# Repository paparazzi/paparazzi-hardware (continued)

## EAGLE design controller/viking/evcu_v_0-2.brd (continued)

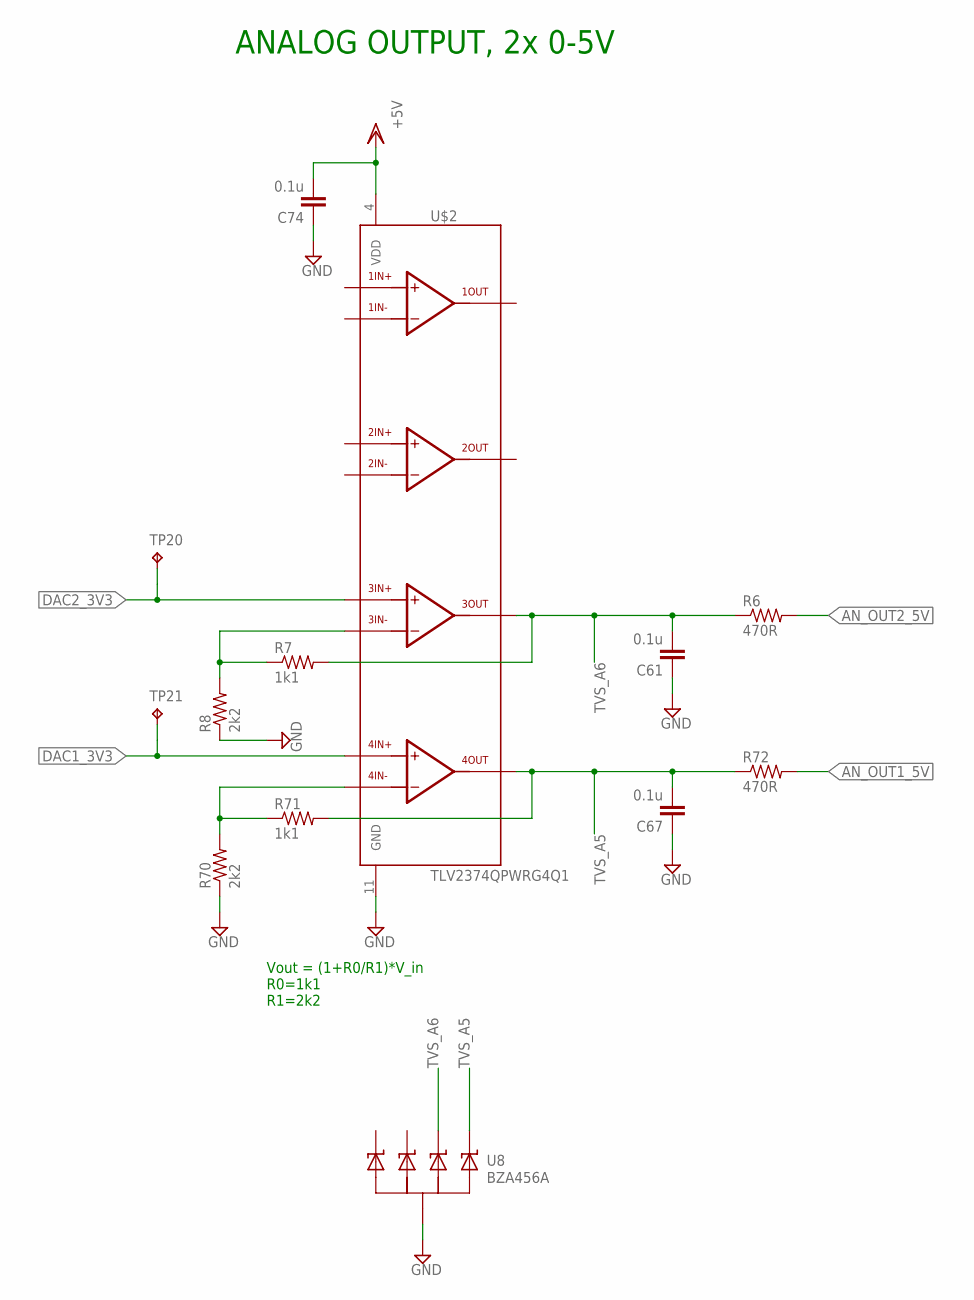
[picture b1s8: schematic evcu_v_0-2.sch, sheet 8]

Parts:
C61, C67, C74: 0.1u; C0603@1
R6, R72: 470R; R0603
R7, R71: 1k1; R0603
R8, R70: 2k2; R0603
TP20, TP21: TPB1,27; B1,27
U8: BZA456A; SOT457R_PHILIPS
U$2: TLV2374QPWRG4Q1; TSSOP14

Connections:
5V: C74.2, U$2.4 (VDD); also elsewhere on the board
AN_OUT1_5V: R72.2; also elsewhere on the board
AN_OUT2_5V: R6.2; also elsewhere on the board
DAC1_3V3: TP21.TP, U$2.12; also elsewhere on the board
DAC2_3V3: TP20.TP, U$2.10; also elsewhere on the board
GND: C61.1, C67.1, C74.1, R8.1, R70.1, U8.2 (COM), U8.5 (COM), U$2.11 (GND); also elsewhere on the board
unnamed: R7.1, R8.2, U$2.9
unnamed: R70.2, R71.1, U$2.13
TVS_A5: C67.2, R71.2, R72.1, U8.6 (C4), U$2.14
TVS_A6: C61.2, R6.1, R7.2, U8.4 (C3), U$2.8

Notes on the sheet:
ANALOG OUTPUT, 2x 0-5V
Vout = (1+R0/R1)*V_in R0=1k1 R1=2k2

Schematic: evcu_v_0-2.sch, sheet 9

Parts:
U$5: DEUTSCH_48_PIN

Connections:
5V: U$5.A$2, U$5.A$5, U$5.A$8, U$5.A$11; also elsewhere on the board
ANALOG_IN1_5V: U$5.A$3; also elsewhere on the board
ANALOG_IN2_5V: U$5.A$6; also elsewhere on the board
ANALOG_IN3_5V: U$5.A$9; also elsewhere on the board
ANALOG_IN4_5V: U$5.A$12; also elsewhere on the board
AN_OUT1_5V: U$5.C$2; also elsewhere on the board
AN_OUT2_5V: U$5.C$4; also elsewhere on the board
CAN1_H: U$5.C$7; also elsewhere on the board
CAN1_L: U$5.C$8; also elsewhere on the board
CAN2_H: U$5.C$11; also elsewhere on the board
CAN2_L: U$5.C$12; also elsewhere on the board
DIN_STB1: U$5.B$7; also elsewhere on the board
DIN_STB2: U$5.B$8; also elsewhere on the board
DIN_STB3: U$5.B$9; also elsewhere on the board
DIN_STB4: U$5.B$10; also elsewhere on the board
DIN_STB5: U$5.B$11; also elsewhere on the board
DIN_STB6: U$5.B$12; also elsewhere on the board
DIN_STG1: U$5.B$2; also elsewhere on the board
DIN_STG2: U$5.B$4; also elsewhere on the board
DOUT_HS1_12V: U$5.D$11; also elsewhere on the board
DOUT_HS2_12V: U$5.D$12; also elsewhere on the board
DOUT_LS1: U$5.D$7; also elsewhere on the board
DOUT_LS2: U$5.D$8; also elsewhere on the board
DOUT_LS3: U$5.D$9; also elsewhere on the board
DOUT_LS4: U$5.D$10; also elsewhere on the board
GND: U$5.A$1, U$5.A$4, U$5.A$7, U$5.A$10, U$5.B$1, U$5.B$3, U$5.B$5, U$5.C$1, U$5.C$3, U$5.C$5, U$5.C$9, U$5.D$1, U$5.D$4; also elsewhere on the board
RS232_1_DIN: U$5.D$2; also elsewhere on the board
RS232_1_DOUT: U$5.D$3; also elsewhere on the board
RS232_2_DIN: U$5.D$5; also elsewhere on the board
RS232_2_DOUT: U$5.D$6; also elsewhere on the board
VIN(+12V): U$5.B$6, U$5.C$6, U$5.C$10; also elsewhere on the board

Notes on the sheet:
DEUTSCH 48pin header DEUTSCH EEC-5X650B DEUTSCH DT13-48PABCD-R015

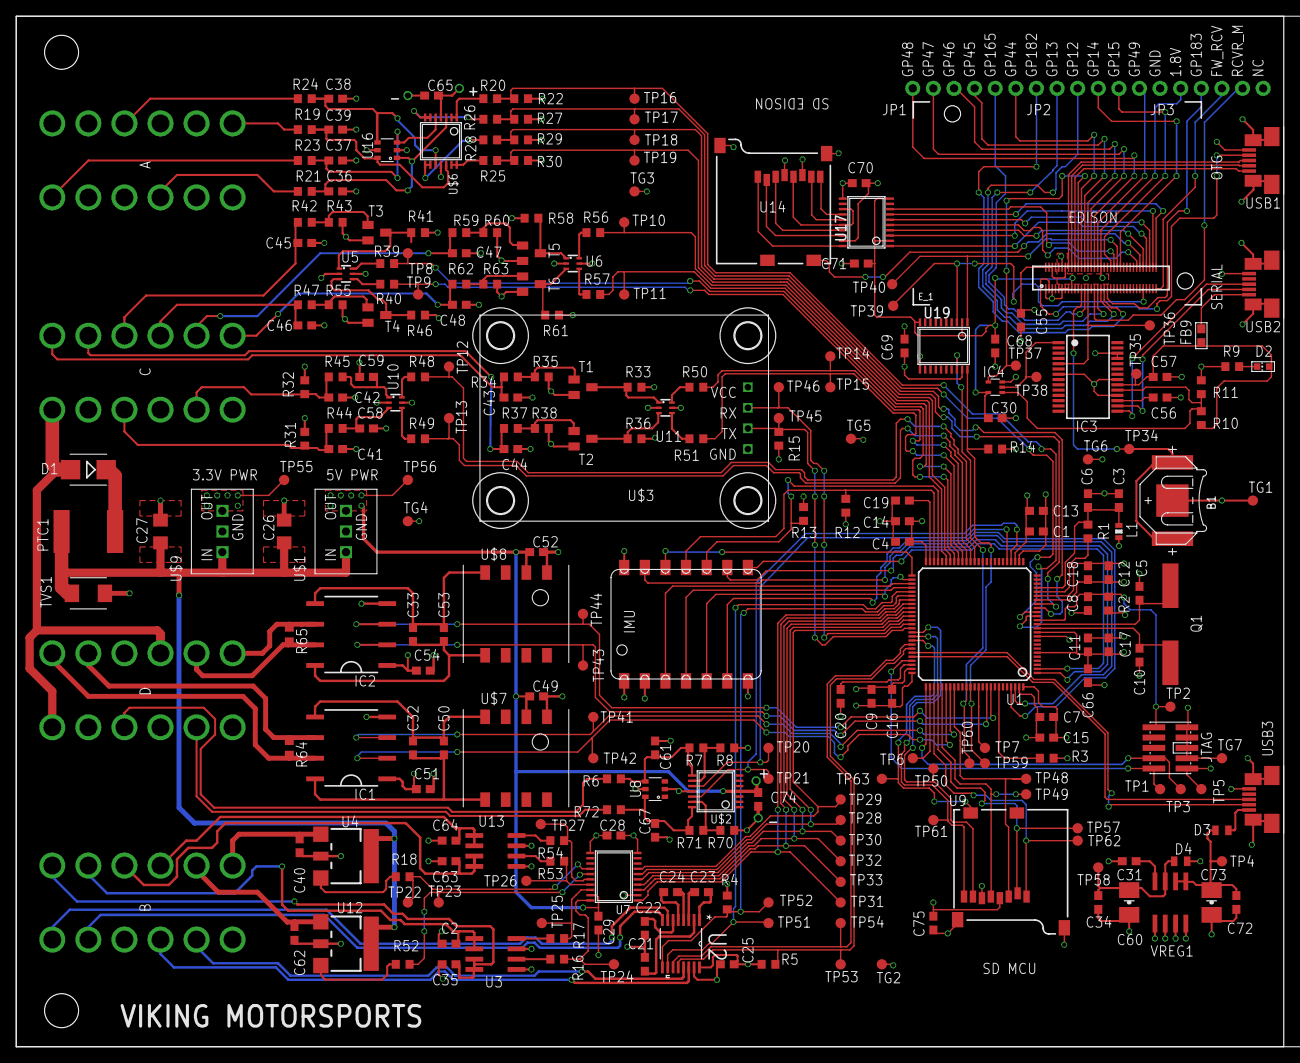
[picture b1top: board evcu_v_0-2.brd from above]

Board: 4 copper layers, 156.2 x 127.0 mm, 267 parts (0 on the bottom side), 204 nets.

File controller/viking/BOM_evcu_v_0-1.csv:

Qty;Value;Device;Package;Parts;Description;DIGIKEY;DM;DNP;DR;DX;DY;MF;MPN;OC_FARNELL;OC_NEWARK;PACKAGE;PARTNO;SHEETNO;SUPPLIER;TP_SIGNAL_NAME;;;;;;;;;;;;;;;;;;;;;;;;;;;;;;;;;;;;;;;;;;;;;;;;;;
1;2920L185DR;2920L;2920L;PTC1;;;;;;;;;;;;;;;;;;;;;;;;;;;;;;;;;;;;;;;;;;;;;;;;;;;;;;;;;;;;;;;;;;
1;330R;R-US_R0603;R0603;R9;RESISTOR; American symbol;;;;;;;;;;;;;;;;;;;;;;;;;;;;;;;;;;;;;;;;;;;;;;;;;;;;;;;;;;;;;;;;
1;36-2998-ND;COIN_CELL_6.8MM;BATTERY_6.8MM-2998;B1;;;;;;;;;;;;;;;;;;;;;;;;;;;;;;;;;;;;;;;;;;;;;;;;;;;;;;;;;;;;;;;;;;
1;47R;R-US_R0603;R0603;R1;RESISTOR; American symbol;;;;;;;;;;;;;;;;;;;;;;;;;;;;;;;;;;;;;;;;;;;;;;;;;;;;;;;;;;;;;;;;
1;600R;INDUCTOR-0603;0603-IND;L1;;;;;;;;;;;;;;;;;;;;;;;;;;;;;;;;;;;;;;;;;;;;;;;;;;;;;;;;;;;;;;;;;;
1;600R 1A;FB0603;C0603;FB9;;;;;;;;;;;;;;;;;;;;;;;;;;;;;;;;;;;;;;;;;;;;;;;;;;;;;;;;;;;;;;;;;;
1;74AHC1G126DCK;74AHC1G126DCK;SC70-5;IC4;Single Bus Buffer Gate With 3-State Outputs;;;;;;;;;;;;;;;;;;;;;;;;;;;;;;;;;;;;;;;;;;;;;;;;;;;;;;;;;;;;;;;;;
1;ABLS-25MHz;CSM-7X-DU;CSM-7X-DU;Q1;SMD CRYSTAL;;;;;;;;;unknown;unknown;;;;;;;;;;;;;;;;;;;;;;;;;;;;;;;;;;;;;;;;;;;;;;;;;;;;;;;
1;ASPIRIN;ASPIRIN;ASPIRIN_1;IMU;;;;;;;;;;;;;ASP6000;;;;;;;;;;;;;;;;;;;;;;;;;;;;;;;;;;;;;;;;;;;;;;;;;;;;;
1;B360B-13-F;DIODE-SMB;SMB;D1;DIODE;;;;;;;;;;;;;;;;;;;;;;;;;;;;;;;;;;;;;;;;;;;;;;;;;;;;;;;;;;;;;;;;;
1;DEUTSCH_48_PIN;DEUTSCH_48_PIN;DEUTSCH_48_PIN;U$5;;;;;;;;;;;;;;;;;;;;;;;;;;;;;;;;;;;;;;;;;;;;;;;;;;;;;;;;;;;;;;;;;;
1;EDISON_CONNECTOR_SEGMENTED;EDISON_CONNECTOR_SEGMENTED;EDISON_DAUGHTER;E_1;;;;;;;;;;;;;;;;;;;;;;;;;;;;;;;;;;;;;;;;;;;;;;;;;;;;;;;;;;;;;;;;;;
1;FT232RL;FT232RL;SSOP28;IC3;Source: http://www.ftdichip.com/Documents/DataSheets/DS_FT232R_v104.pdf;;;;;;;;FT232RL;1146032;91K9918;;;;;;;;;;;;;;;;;;;;;;;;;;;;;;;;;;;;;;;;;;;;;;;;;;;;;;;
1;GPS_UBLOX;GPS_UBLOX;GPS_UBLOX;U$3;;;;;;;;;;;;;;;;;;;;;;;;;;;;;;;;;;;;;;;;;;;;;;;;;;;;;;;;;;;;;;;;;;
1;GREEN;LED0603;D0603;D2;;;0;;90;57.2;1.8;;;;;;;4;;;;;;;;;;;;;;;;;;;;;;;;;;;;;;;;;;;;;;;;;;;;;;;;;;;;
1;OKI-78SR-3.3/1.5-W36-C;OKI-78SR-3.3/1.5-W36-C;OKI-78SR;U$9;;;;;;;;;;;;;;;;;;;;;;;;;;;;;;;;;;;;;;;;;;;;;;;;;;;;;;;;;;;;;;;;;;
1;OKI-78SR-5/1.5-W36-C;OKI-78SR-5/1.5-W36-C;OKI-78SR;U$1;;;;;;;;;;;;;;;;;;;;;;;;;;;;;;;;;;;;;;;;;;;;;;;;;;;;;;;;;;;;;;;;;;
1;PIN_HDR_EDG_1.27MM_5-2;CONN_5-2-FTSH-V;FTSH-105-DV;JTAG;;;;T;;;;;;;;;conn-smd-0.05in-5-2;;;;;;;;;;;;;;;;;;;;;;;;;;;;;;;;;;;;;;;;;;;;;;;;;;;;;
1;SMBJ20CA-TR;SUPPRESSOR-SMBJ;SMBJ;TVS1;Suppressor diode;;;;;;;;;;;;SM30T35AY;;;;;;;;;;;;;;;;;;;;;;;;;;;;;;;;;;;;;;;;;;;;;;;;;;;;;
1;STM32F207VC;STM32F207VC;LQFP100;U1;STM32F207VC;;;;;;;;;;;;;;;;;;;;;;;;;;;;;;;;;;;;;;;;;;;;;;;;;;;;;;;;;;;;;;;;;
1;TRS3232EQPWRQ1;TRS3232EQPWRQ1;SOP65P640X120-16N;U2;RS-232 LINE DRIVER/RECEIVER;296-24863-1-ND;;;;;;;TRS3232EQPWRQ1;0;09R6724;TSSOP-16;;;Texas Instruments;;;;;;;;;;;;;;;;;;;;;;;;;;;;;;;;;;;;;;;;;;;;;;;;;;;
2;100p;C-EUC0603;C0603@1;C58; C59;CAPACITOR; European symbol;;;;;;;;;;;;;;;;;;;;;;;;;;;;;;;;;;;;;;;;;;;;;;;;;;;;;;;;;;;;;;;
2;10u; 25V; X5R;C-EUC0603;C0603@1;C50; C53;CAPACITOR; European symbol;;;;;;;;;;;;;;;;;;;;;;;;;;;;;;;;;;;;;;;;;;;;;;;;;;;;;;;;;;;;;
2;120R; 1%;R-US_R0603;R0603;R64; R65;RESISTOR; American symbol;;;;;;;;;;;;;;;;;;;;;;;;;;;;;;;;;;;;;;;;;;;;;;;;;;;;;;;;;;;;;;
2;2.2u;C-EUC0603;C0603@1;C19; C20;CAPACITOR; European symbol;;;;;;;;;;;;;;;;;;;;;;;;;;;;;;;;;;;;;;;;;;;;;;;;;;;;;;;;;;;;;;;
2;22u;C-USC1206;C1206;C26; C27;CAPACITOR; American symbol;;;;;;;;;;;;;;;;;;;;;;;;;;;;;;;;;;;;;;;;;;;;;;;;;;;;;;;;;;;;;;;
2;2k43;R-US_R0603;R0603;R31; R32;RESISTOR; American symbol;;;;;;;;;;;;;;;;;;;;;;;;;;;;;;;;;;;;;;;;;;;;;;;;;;;;;;;;;;;;;;;
2;30p;C-EUC0603;C0603@1;C5; C10;CAPACITOR; European symbol;;;;;;;;;;;;;;;;;;;;;;;;;;;;;;;;;;;;;;;;;;;;;;;;;;;;;;;;;;;;;;;
2;41k7;R-US_R0603;R0603;R44; R45;RESISTOR; American symbol;;;;;;;;;;;;;;;;;;;;;;;;;;;;;;;;;;;;;;;;;;;;;;;;;;;;;;;;;;;;;;;
2;BTS3405G;BTS3405G;SOIC8;U3; U13;Smart Low-Side Power Switch;;;;;;;;;;;;;;;;;;;;;;;;;;;;;;;;;;;;;;;;;;;;;;;;;;;;;;;;;;;;;;;;
2;BZA456A;BZA456A;SOT457R_PHILIPS;U8; U16;BZA456A;;;;;;;;;;;;;;;;;;;;;;;;;;;;;;;;;;;;;;;;;;;;;;;;;;;;;;;;;;;;;;;;
2;ISO1050DUB;ISO1050DUB;DUB-R-PDSO-G8;IC1; IC2;ISOLATED CAN TRANSCEIVER;;;;;;;;ISO1050DUBR;1755712;14R9899;;;;;;;;;;;;;;;;;;;;;;;;;;;;;;;;;;;;;;;;;;;;;;;;;;;;;;
2;ISP452;ISP452;SOT223-W;U4; U12;ISP 452;;;;;;;;;;;;;;;;;;;;;;;;;;;;;;;;;;;;;;;;;;;;;;;;;;;;;;;;;;;;;;;;
2;MOLEX-47346-0001;MOLEX-47346-0001;MOLEX-47364-0001;USB1; USB2;MICRO USB B; BOTTOM MOUNT;;;;;;;;;;;;;;;;;;;;;;;;;;;;;;;;;;;;;;;;;;;;;;;;;;;;;;;;;;;;;;;
2;R1SE;R1SE;R1SE;U$7; U$8;;;;;;;;;;;;;;;;;;;;;;;;;;;;;;;;;;;;;;;;;;;;;;;;;;;;;;;;;;;;;;;;;
2;TLV2374QPWRG4Q1;TLV2374QPWRG4Q1;TSSOP14;U$2; U$6;;;;;;;;;;;;;;;;;;;;;;;;;;;;;;;;;;;;;;;;;;;;;;;;;;;;;;;;;;;;;;;;;
2;USD-SOCKETNEW;USD-SOCKETNEW;MICRO-SD-SOCKET-PP;U9; U14;microSD Socket;;;;;;;;;;;;;;;;;;;;;;;;;;;;;;;;;;;;;;;;;;;;;;;;;;;;;;;;;;;;;;;;
3;TXB0108;TXB0108;UFDFN-20;U7; U17; U19;;;;;;;;;;;;;;;;;;;;;;;;;;;;;;;;;;;;;;;;;;;;;;;;;;;;;;;;;;;;;;;;
4;74LVC2G17;74LVC2G17;SOT363_INFINEON;U5; U6; U10; U11;74LVC2G17;;;;;;;;;;;;;;;;;;;;;;;;;;;;;;;;;;;;;;;;;;;;;;;;;;;;;;;;;;;;;;
6;1k1;R-US_R0603;R0603;R7; R20; R25; R26; R28; R71;RESISTOR; American symbol;;;;;;;;;;;;;;;;;;;;;;;;;;;;;;;;;;;;;;;;;;;;;;;;;;;;;;;;;;;
6;2k2;R-US_R0603;R0603;R8; R22; R27; R29; R30; R70;RESISTOR; American symbol;;;;;;;;;;;;;;;;;;;;;;;;;;;;;;;;;;;;;;;;;;;;;;;;;;;;;;;;;;;
6;DK:MMBT3904LT1GOSCT-ND;-NPN-SOT23-EBC;SOT23-EBC;T1; T2; T3; T4; T5; T6;NPN Transistror;;;;;;;;;;;;;;;;;;;;;;;;;;;;;;;;;;;;;;;;;;;;;;;;;;;;;;;;;;;;
7;1u;C-EUC0603;C0603@1;C1; C3; C4; C7; C9; C11; C12;CAPACITOR; European symbol;;;;;;;;;;;;;;;;;;;;;;;;;;;;;;;;;;;;;;;;;;;;;;;;;;;;;;;;;;
7;4k7;R-US_R0603;R0603;R10; R35; R38; R43; R55; R60; R63;RESISTOR; American symbol;;;;;;;;;;;;;;;;;;;;;;;;;;;;;;;;;;;;;;;;;;;;;;;;;;;;;;;;;;
8;1000p;C-EUC0603;C0603@1;C41; C42; C43; C44; C45; C46; C47; C48;CAPACITOR; European symbol;;;;;;;;;;;;;;;;;;;;;;;;;;;;;;;;;;;;;;;;;;;;;;;;;;;;;;;;;
8;1k;R-US_R0603;R0603;R39; R40; R48; R49; R50; R51; R56; R57;RESISTOR; American symbol;;;;;;;;;;;;;;;;;;;;;;;;;;;;;;;;;;;;;;;;;;;;;;;;;;;;;;;;;
8;470R;R-US_R0603;R0603;R6; R16; R17; R18; R52; R53; R54; R72;RESISTOR; American symbol;;;;;;;;;;;;;;;;;;;;;;;;;;;;;;;;;;;;;;;;;;;;;;;;;;;;;;;;;
23;10k;R-US_R0603;R0603;R2; R3; R4; R5; R11; R14; R15; R19; R21; R23; R24; R33; R34; R36; R37; R41; R42; R46; R47; R58; R59; R61; R62;RESISTOR; American symbol;;;;;;;;;;;;;;;;;;;;;;;;;;;;;;;;;;;;;;;;;;
43;0.1u;C-EUC0603;C0603@1;C2; C6; C8; C13; C14; C15; C16; C17; C18; C21; C22; C23; C24; C25; C28; C29; C30; C32; C33; C35; C36; C37; C38; C39; C40; C49; C51; C52; C54; C55; C56; C57; C61; C62; C63; C64; C65; C66; C67; C68; C69; C70; C71;CAPACITOR; European symbol;;;;;;;;;;;;;;;;;;;;;;
63;TPB1;27;TPB1;27;B1;27;TG1; TG2; TG3; TG4; TG5; TG6; TP1; TP2; TP3; TP4; TP5; TP6; TP7; TP8; TP9; TP10; TP11; TP12; TP13; TP14; TP15; TP16; TP17; TP18; TP19; TP20; TP21; TP22; TP23; TP24; TP25; TP26; TP27; TP28; TP29; TP30; TP31; TP32; TP33; TP34; TP35; TP36; TP37; TP38; TP39; TP40; TP41; TP42; TP43; TP44; TP45; TP46; TP47; TP48; TP49; TP50; TP51; TP52; TP53; TP54; TP55; TP56; TP57;Test pad

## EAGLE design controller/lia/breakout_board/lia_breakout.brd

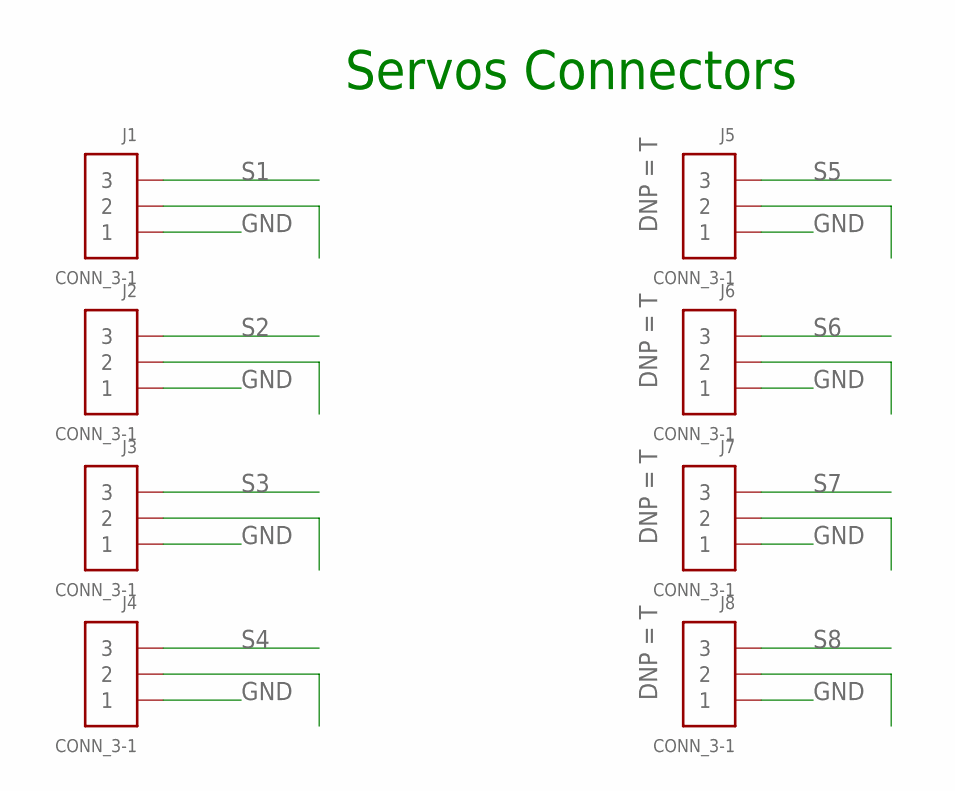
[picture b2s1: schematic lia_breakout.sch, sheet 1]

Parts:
J1, J2, J3, J4, J5, J6, J7, J8: CONN_3-1; SIP1X3_100; PARTNO conn-th-0.1in-3-2-ra

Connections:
GND: J1.1, J2.1, J3.1, J4.1, J5.1, J6.1, J7.1, J8.1; also elsewhere on the board
S1: J1.3
S2: J2.3
S3: J3.3
S4: J4.3
S5: J5.3
S6: J6.3
S7: J7.3
S8: J8.3

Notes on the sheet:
Servos Connectors

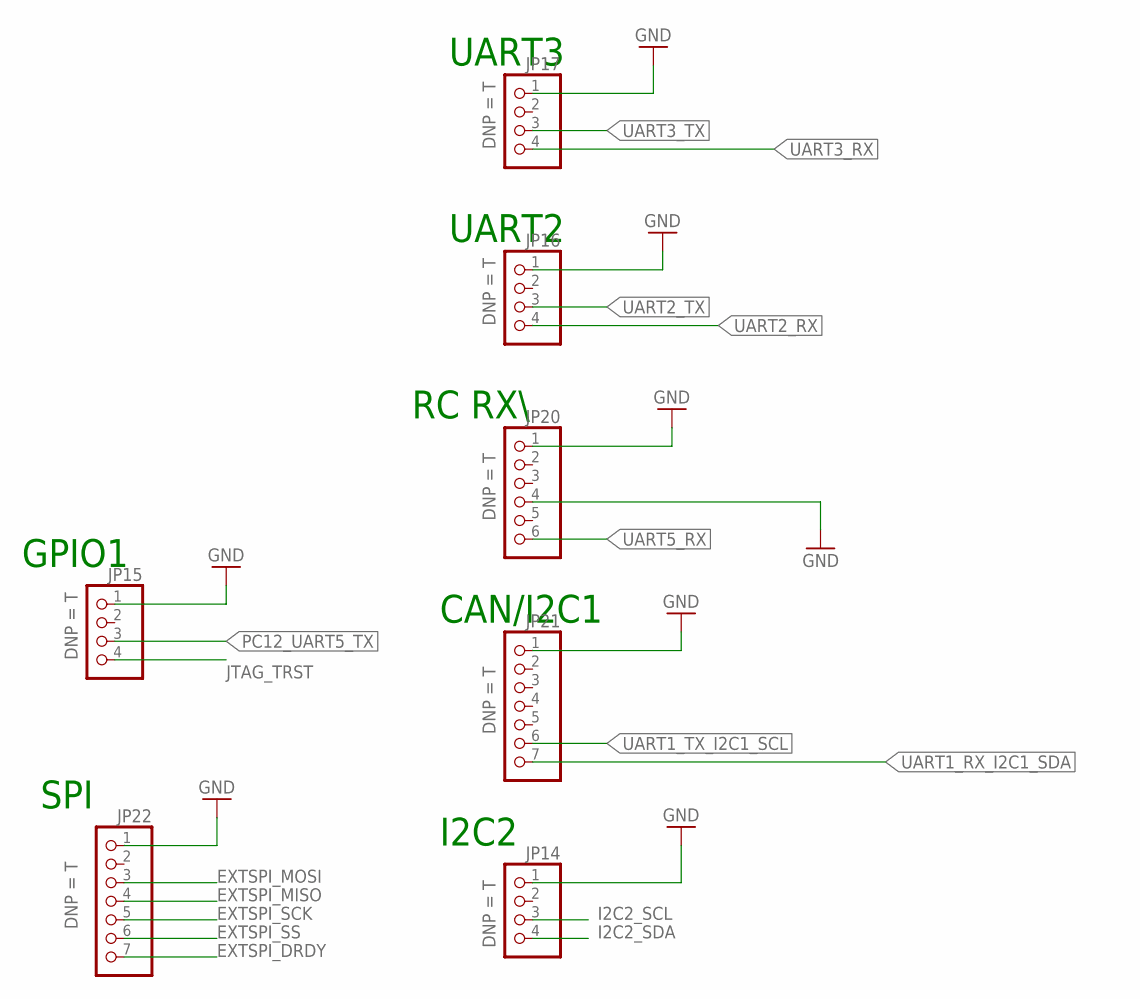
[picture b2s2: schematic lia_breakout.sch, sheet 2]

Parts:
JP14, JP15, JP16, JP17: PINHD-1X4; 1X04; PARTNO conn-th-0.1in-4-1
JP20: PINHD-1X6; 1X06; PARTNO conn-th-0.1in-6-1
JP21, JP22: PINHD-1X7; 1X07; PARTNO conn-th-0.1in-7-1

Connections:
EXTSPI_DRDY: JP22.7
EXTSPI_MISO: JP22.4
EXTSPI_MOSI: JP22.3
EXTSPI_SCK: JP22.5
EXTSPI_SS: JP22.6
GND: JP14.1, JP15.1, JP16.1, JP17.1, JP20.1, JP20.4, JP21.1, JP22.1; also elsewhere on the board
I2C2_SCL: JP14.3
I2C2_SDA: JP14.4
JTAG_TRST: JP15.4
PC12_UART5_TX: JP15.3; also elsewhere on the board
UART1_RX_I2C1_SDA: JP21.7; also elsewhere on the board
UART1_TX_I2C1_SCL: JP21.6; also elsewhere on the board
UART2_RX: JP16.4; also elsewhere on the board
UART2_TX: JP16.3; also elsewhere on the board
UART3_RX: JP17.4; also elsewhere on the board
UART3_TX: JP17.3; also elsewhere on the board
UART5_RX: JP20.6; also elsewhere on the board

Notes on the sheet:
SPI
I2C2
GPIO1
UART3
UART2
RC RX\
CAN/I2C1

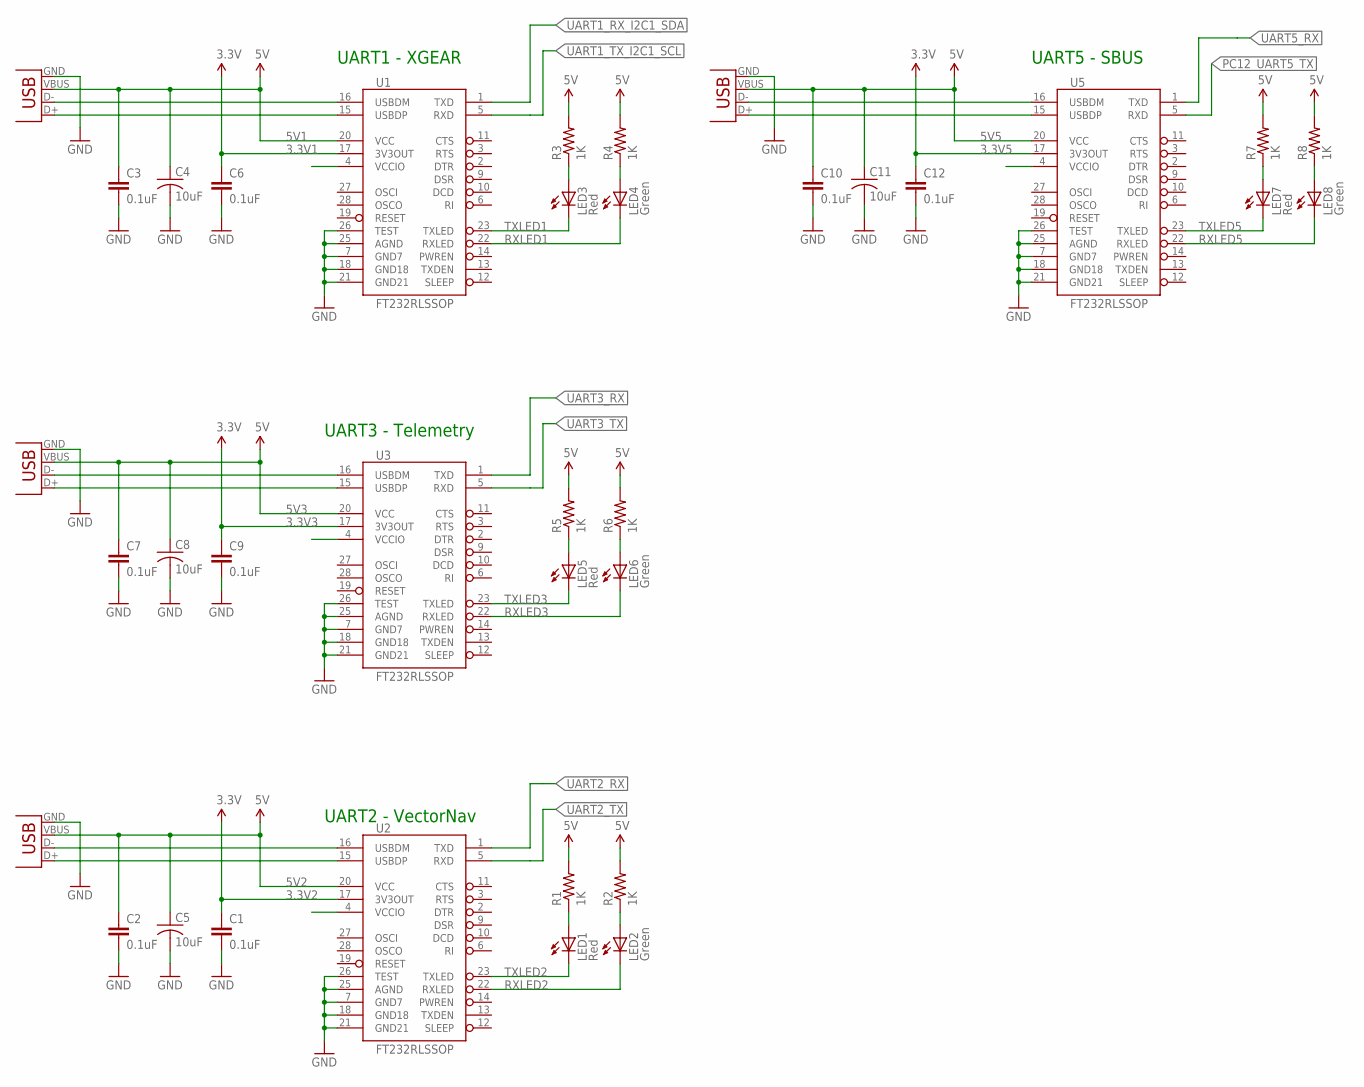
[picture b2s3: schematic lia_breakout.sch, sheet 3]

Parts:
C1, C2, C3, C6, C7, C9, C10, C12: 0.1uF; 0603-CAP
C4, C5, C8, C11: 10uF; C0603
LED1, LED3, LED5, LED7: Red; LED-0603
LED2, LED4, LED6, LED8: Green; LED-0603
R1, R2, R3, R4, R5, R6, R7, R8: 1K; 0603-RES
U1, U2, U3, U5: FT232RLSSOP; SSOP28DB
X1, X2, X3, X4: USB-SMD-NS; USB-MINIB-NOSTOP

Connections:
3.3V1: C6.1, U1.17 (3V3OUT)
3.3V2: C1.1, U2.17 (3V3OUT)
3.3V3: C9.1, U3.17 (3V3OUT)
3.3V5: C12.1, U5.17 (3V3OUT)
5V1: C3.1, C4.1, R3.2, R4.2, U1.20 (VCC), X1.VBUS
5V2: C2.1, C5.1, R1.2, R2.2, U2.20 (VCC), X2.VBUS
5V3: C7.1, C8.1, R5.2, R6.2, U3.20 (VCC), X3.VBUS
5V5: C10.1, C11.1, R7.2, R8.2, U5.20 (VCC), X4.VBUS
GND: C1.2, C2.2, C3.2, C4.2, C5.2, C6.2, C7.2, C8.2, C9.2, C10.2, C11.2, C12.2, U1.7 (GND7), U1.18 (GND18), U1.21 (GND21), U1.25 (AGND), U1.26 (TEST), U2.7 (GND7), U2.18 (GND18), U2.21 (GND21), U2.25 (AGND), U2.26 (TEST), U3.7 (GND7), U3.18 (GND18), U3.21 (GND21), U3.25 (AGND), U3.26 (TEST), U5.7 (GND7), U5.18 (GND18), U5.21 (GND21), U5.25 (AGND), U5.26 (TEST), X1.GND, X2.GND, X3.GND, X4.GND; also elsewhere on the board
unnamed: LED1.A, R1.1
unnamed: LED2.A, R2.1
unnamed: LED3.A, R3.1
unnamed: LED4.A, R4.1
unnamed: LED5.A, R5.1
unnamed: LED6.A, R6.1
unnamed: LED7.A, R7.1
unnamed: LED8.A, R8.1
PC12_UART5_TX: U5.5 (RXD); also elsewhere on the board
RXLED1: LED4.C, U1.22 (RXLED)
RXLED2: LED2.C, U2.22 (RXLED)
RXLED3: LED6.C, U3.22 (RXLED)
RXLED5: LED8.C, U5.22 (RXLED)
TXLED1: LED3.C, U1.23 (TXLED)
TXLED2: LED1.C, U2.23 (TXLED)
TXLED3: LED5.C, U3.23 (TXLED)
TXLED5: LED7.C, U5.23 (TXLED)
UART1_RX_I2C1_SDA: U1.1 (TXD); also elsewhere on the board
UART1_TX_I2C1_SCL: U1.5 (RXD); also elsewhere on the board
UART2_RX: U2.1 (TXD); also elsewhere on the board
UART2_TX: U2.5 (RXD); also elsewhere on the board
UART3_RX: U3.1 (TXD); also elsewhere on the board
UART3_TX: U3.5 (RXD); also elsewhere on the board
UART5_RX: U5.1 (TXD); also elsewhere on the board
USB_D+: U2.15 (USBDP), X2.D+
USB_D+1: U1.15 (USBDP), X1.D+
USB_D+2: U3.15 (USBDP), X3.D+
USB_D+3: U5.15 (USBDP), X4.D+
USB_D-: U2.16 (USBDM), X2.D-
USB_D-1: U1.16 (USBDM), X1.D-
USB_D-2: U3.16 (USBDM), X3.D-
USB_D-3: U5.16 (USBDM), X4.D-

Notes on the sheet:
UART1 - XGEAR
UART3 - Telemetry
UART2 - VectorNav
UART5 - SBUS

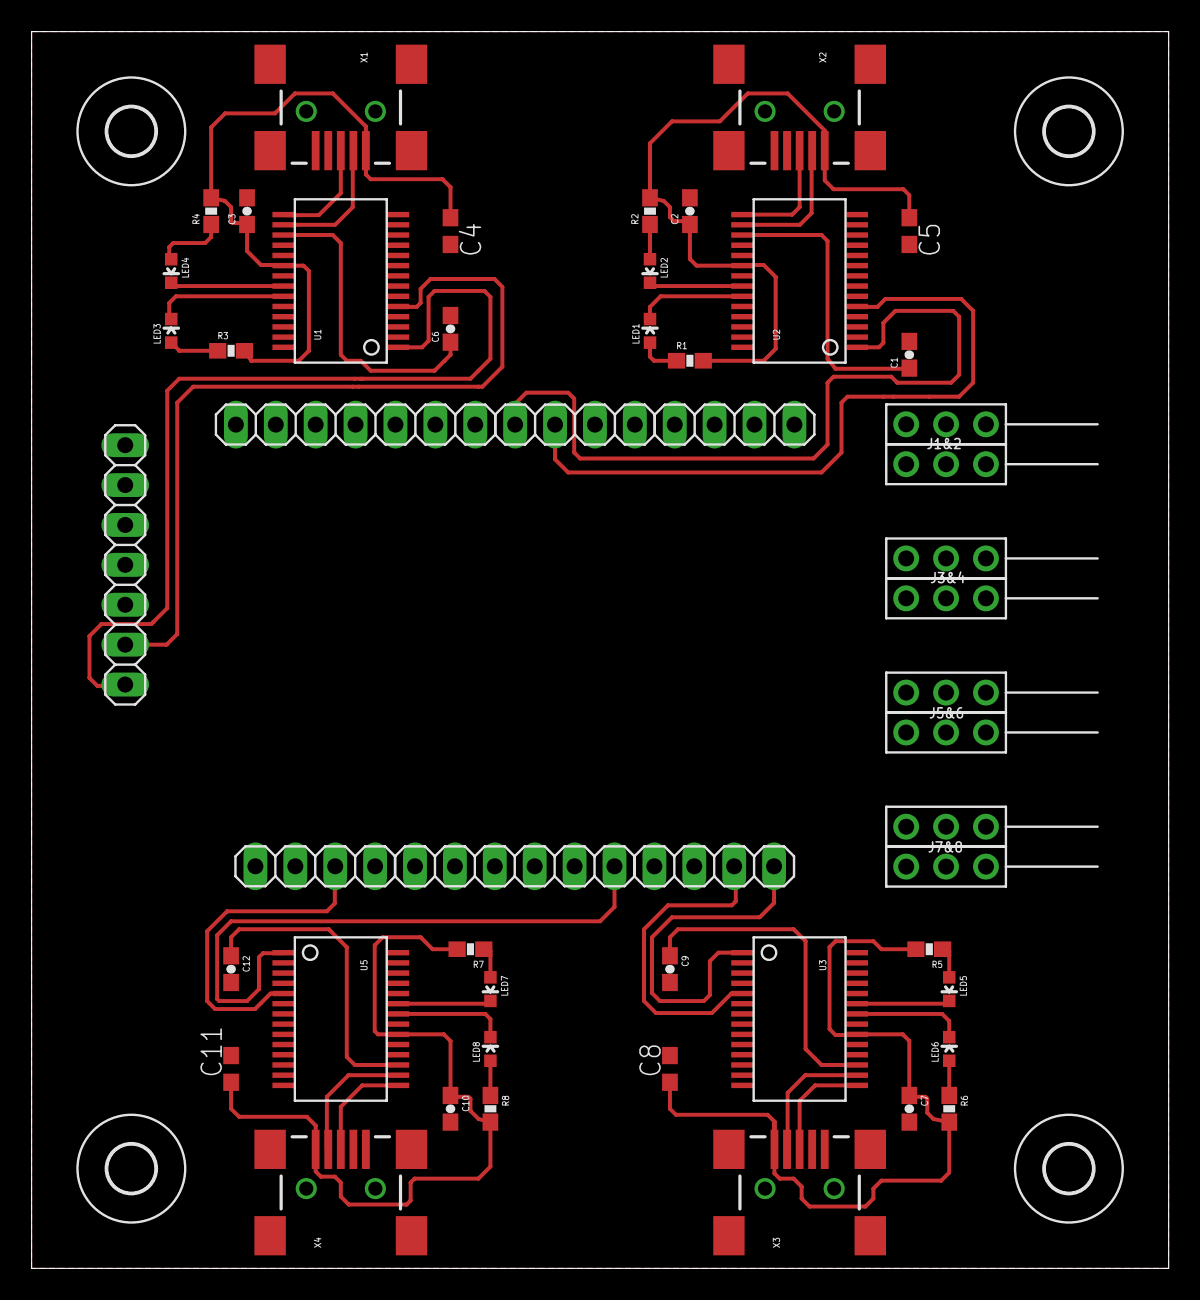
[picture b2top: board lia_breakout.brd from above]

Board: 2 copper layers, 72.4 x 78.7 mm, 55 parts (0 on the bottom side), 41 nets.

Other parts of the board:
U$13, U$14, U$15, U$16: 3,0

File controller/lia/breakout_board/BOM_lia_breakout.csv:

Qty;Value;Device;Package;Parts;Description;DNP;MFR-PN;PARTNO
4;;PINHD-1X4;1X04;JP14, JP15, JP16, JP17;PIN HEADER;T;;conn-th-0.1in-4-1
1;;PINHD-1X6;1X06;JP20;PIN HEADER;T;;conn-th-0.1in-6-1
2;;PINHD-1X7;1X07;JP21, JP22;PIN HEADER;T;;conn-th-0.1in-7-1
8;0.1uF;CAP0603-CAP;0603-CAP;C1, C2, C3, C6, C7, C9, C10, C12;Capacitor;;;
4;10uF;CAP_POL1206;EIA3216;C4, C5, C8, C11;Capacitor Polarized;;;
8;1K;RESISTOR0603-RES;0603-RES;R1, R2, R3, R4, R5, R6, R7, R8;Resistor;;;
4;CONN_3-1;CONN_3-1;SIP1X3_100;J1, J2, J3, J4;;;;conn-th-0.1in-3-2-ra
4;CONN_3-1;CONN_3-1;SIP1X3_100;J5, J6, J7, J8;;T;;conn-th-0.1in-3-2-ra
4;FT232RLSSOP;FT232RLSSOP;SSOP28DB;U1, U2, U3, U5;USB UART;;;
4;Green;LED0603;LED-0603;LED2, LED4, LED6, LED8;LEDs;;;
4;Red;LED0603;LED-0603;LED1, LED3, LED5, LED7;LEDs;;;
4;USB-SMD-NS;USB-SMD-NS;USB-MINIB-NOSTOP;X1, X2, X3, X4;USB Connectors;;;
